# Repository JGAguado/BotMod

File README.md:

[![GitHub Release][releases-shield]][releases]
[![License][license-shield]](LICENSE)

[![Project Maintenance][maintenance-shield]][maintenance]
[![BuyMeCoffee][buymecoffee-shield]][buymecoffee]

# BotMod
Mod for ArduLab, directly plugable via the Mod Interface. The BotMod is designed to enhance the ArduLab functions for autonomous vehicles and printed-bots.

## Project tree

<li><a href="./Design/">Design</a></li>
<li><a href="./Documentation/">Documentation</a></li>

<li><a href="./README.md">README.md</a></li>

[releases-shield]: https://img.shields.io/github/release/JGAguado/BotMod.svg?style=for-the-badge
[releases]: https://github.com/JGAguado/BotMod/releases

[license-shield]: https://img.shields.io/badge/License-CC%20BY--NC--SA%204.0-lightgrey.svg?style=for-the-badge

[maintenance-shield]: https://img.shields.io/badge/maintainer-J.%20G.%20Aguado-blue.svg?style=for-the-badge
[maintenance]: https://github.com/JGAguado

[buymecoffee-shield]: https://img.shields.io/badge/buy%20me%20a%20coffee-support-yellow.svg?style=for-the-badge
[buymecoffee]: https://www.buymeacoffee.com/J.G.Aguado

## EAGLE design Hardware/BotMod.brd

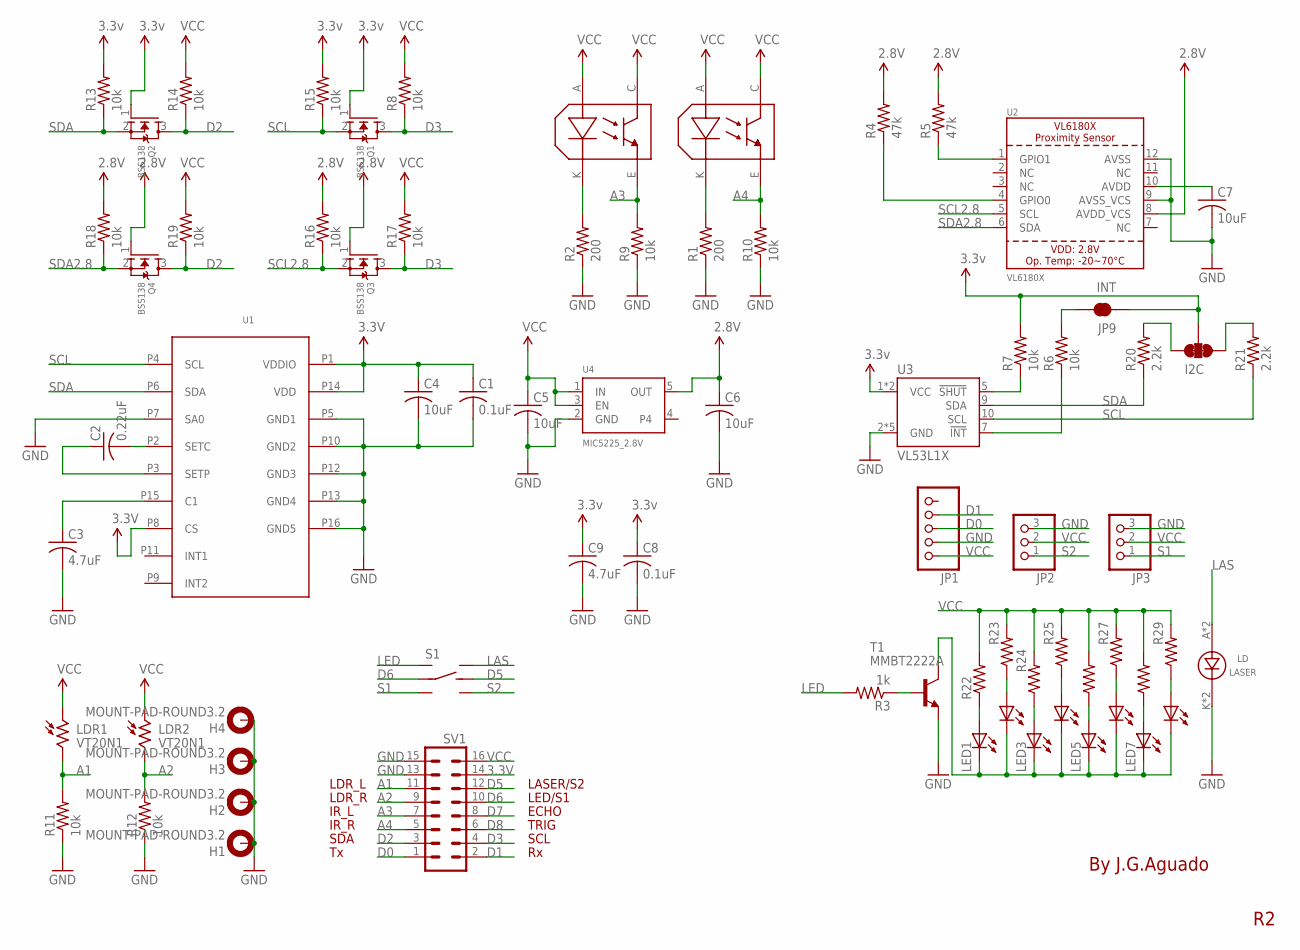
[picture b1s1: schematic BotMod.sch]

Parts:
C1, C8: 0.1uF; 0402
C2: 0.22uF; 0402
C3, C9: 4.7uF; 0402
C4, C5, C6, C7: 10uF; 0402
H1, H2, H3, H4: MOUNT-PAD-ROUND3.2; 3,2-PAD
I2C: JUMPER-SMT_3_2-NC_TRACE_SILK; SMT-JUMPER_3_2-NC_TRACE_SILK
IR1, IR2: IR_TCRT5000
JP1: PINHEAD_5_FEMALE
JP2, JP3: PINHD-1X3; 1X03
JP9: INT; PAD-JUMPER-2-NC_BY_TRACE_YES_SILK
LD: LASER; KEYES_LASER
LDR1, LDR2: VT20N1; TO46-VT200
LED1, LED2, LED3, LED4, LED5, LED6, LED7, LED8: LED5730
Q1, Q2, Q3, Q4: BSS138; SOT23
R1, R2: 200; 0402
R3: 1k; 0402
R4, R5: 47k; 0402
R6, R7, R8, R9, R10, R11, R12, R13, R14, R15, R16, R17, R18, R19: 10k; 0402
R20, R21: 2.2k; 0402
R22, R23, R24, R25, R26, R27, R28, R29: R1206; 1206
S1: DPDT_JS202011CQN
SV1: MA08-2
T1: MMBT2222A; SOT23-BEC
U1: LSM303D; LGA3X3_16L
U2: VL6180X; VL6180
U3: VL53L1X
U4: MIC5225_2.8V; SOT23-5

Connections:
2.8V: C6.1, Q3.1 (G), Q4.1 (G), R4.2, R5.2, R16.2, R18.2, U2.8 (AVDD_VCS), U4.5 (OUT)
3.3V: C1.1, C4.1, C8.1, C9.1, I2C.2, JP9.1, Q1.1 (G), Q2.1 (G), R7.2, R13.2, R15.2, SV1.14, U1.P1 (VDDIO), U1.P8 (CS), U1.P14 (VDD), U3.1 (VCC), U3.11 (VCC)
A1: LDR1.2, R11.2, SV1.11
A2: LDR2.2, R12.2, SV1.9
A3: IR1.E, R9.2, SV1.7
A4: IR2.E, R10.2, SV1.5
D0: JP1.P$3 (3), SV1.1
D1: JP1.P$4 (4), SV1.2
D2: Q2.3 (D), Q4.3 (D), R14.1, R19.1, SV1.3
D3: Q1.3 (D), Q3.3 (D), R8.1, R17.1, SV1.4
D5: S1.5 (RC), SV1.12
D6: S1.2 (LC), SV1.10
D7: SV1.8
D8: SV1.6
GND: C1.2, C3.2, C4.2, C5.2, C6.2, C7.2, C8.2, C9.2, H1.B3,2, H2.B3,2, H3.B3,2, H4.B3,2, JP1.P$2 (2), JP2.3, JP3.3, LD.K, LD.K1 (K), R1.1, R2.1, R9.1, R10.1, R11.1, R12.1, SV1.13, SV1.15, T1.E, U1.P5 (GND1), U1.P7 (SA0), U1.P10 (GND2), U1.P12 (GND3), U1.P13 (GND4), U1.P16 (GND5), U2.9 (AVSS_VCS), U2.12 (AVSS), U3.2 (GND), U3.3 (GND), U3.4 (GND), U3.6 (GND), U3.12 (GND), U4.2 (GND)
L1: LED1.P$1 (A), R22.1
L2: LED2.P$1 (A), R23.1
L3: LED3.P$1 (A), R24.1
L4: LED4.P$1 (A), R25.1
L5: LED5.P$1 (A), R26.1
L6: LED8.P$1 (A), R29.1
L7: LED7.P$1 (A), R28.1
L8: LED6.P$1 (A), R27.1
LAS: LD.A, LD.A1 (A), S1.4 (R1)
LED: R3.2, S1.1 (L1)
unnamed: LED1.P$2 (C), LED2.P$2 (C), LED3.P$2 (C), LED4.P$2 (C), LED5.P$2 (C), LED6.P$2 (C), LED7.P$2 (C), LED8.P$2 (C), T1.C
unnamed: R3.1, T1.B
unnamed: IR1.K, R2.2
unnamed: IR2.K, R1.2
unnamed: R5.1, U2.1 (GPIO1)
unnamed: R4.1, U2.4 (GPIO0)
unnamed: I2C.3, R20.2
unnamed: C7.1, U2.10 (AVDD)
unnamed: I2C.1, R21.2
unnamed: C3.1, U1.P15 (C1)
unnamed: C2.2, U1.P2 (SETC)
unnamed: C2.1, U1.P3 (SETP)
unnamed: JP9.2, R6.2
unnamed: R7.1, U3.5 (!SHUT)
unnamed: R6.1, U3.7 (!INT)
S1: JP3.1, S1.3 (L2)
S2: JP2.1, S1.6 (R2)
SCL: Q1.2 (S), R15.1, R21.1, U1.P4 (SCL), U3.10 (SCL)
SCL2.8: Q3.2 (S), R16.1, U2.5 (SCL)
SDA: Q2.2 (S), R13.1, R20.1, U1.P6 (SDA), U3.9 (SDA)
SDA2.8: Q4.2 (S), R18.1, U2.6 (SDA)
VCC: C5.1, IR1.A, IR1.C, IR2.A, IR2.C, JP1.P$1 (1), JP2.2, JP3.2, LDR1.1, LDR2.1, R8.2, R14.2, R17.2, R19.2, R22.2, R23.2, R24.2, R25.2, R26.2, R27.2, R28.2, R29.2, SV1.16, U4.1 (IN), U4.3 (EN)

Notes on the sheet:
SCL
By J.G.Aguado
SDA
LDR_L
LDR_R
IR_R
IR_L
TRIG
ECHO
LED/S1
LASER/S2

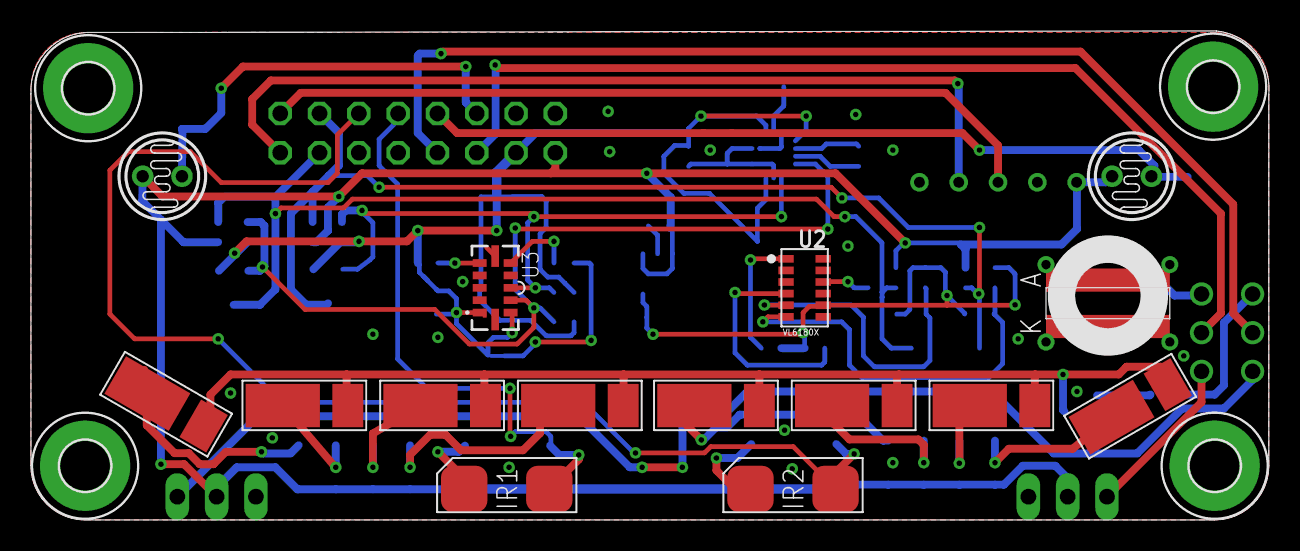
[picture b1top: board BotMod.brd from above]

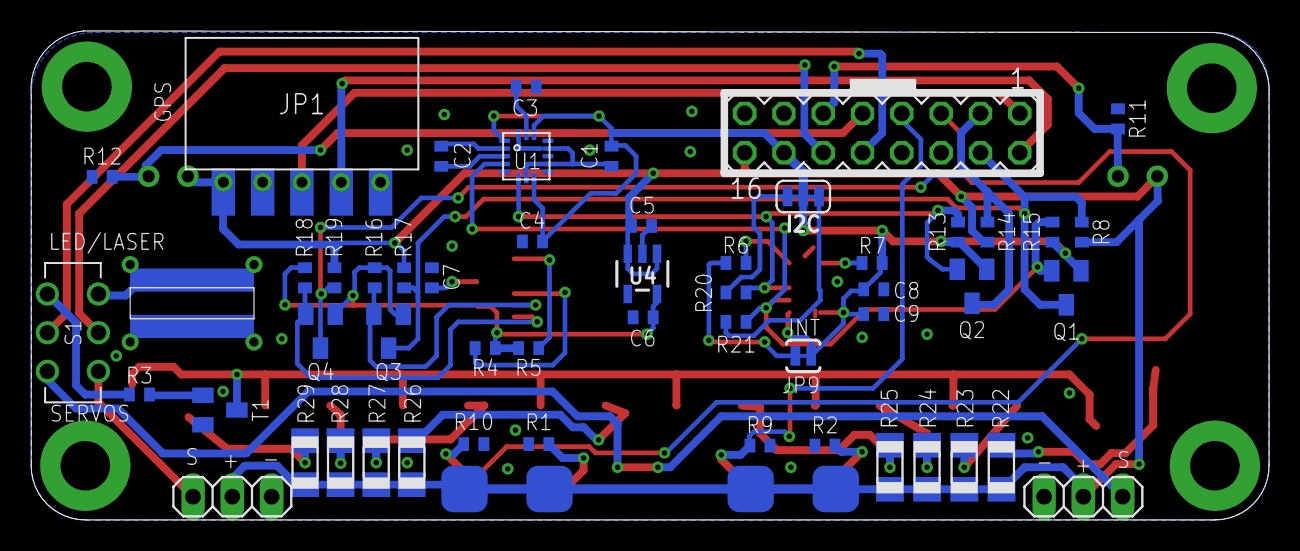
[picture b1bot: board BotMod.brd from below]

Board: 2 copper layers, 80.0 x 31.6 mm, 71 parts (52 on the bottom side), 45 nets.

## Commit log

2018-01-10 Laser resistor removed
2018-01-12 Mod connector updated to 16 pin
2018-01-14 SCH and BRD updated Production Files (GERBER, BOM and Centroid)
2018-01-17 Update gerber for production
2018-02-03 Added Schematic.pdf
2018-02-09 Updated centroid file
2018-04-29 Updated design files: - Added support for GPS through Serial port - Silkscreen layouts improved
2018-04-29 Production files updated
2018-05-02 Centroid file updated
2018-05-02 Updated documentation
2020-01-24 Redesigned BotMod (R2) with support for: - ToF distance sensors VL6180X (5-100mm) and VL53L1X (40-4000mm) - SMD High Intensity Led
2020-02-07 Updated LED Resistors
2020-02-28 Replaced LED lights with 7310 package
2020-02-28 Silkscreen files added
2020-02-28 Updated Production files
2020-05-10 Updated Design Files
2020-05-10 Removed Production zip
2022-04-15 Updated structure

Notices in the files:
parts and their libraries:
microbuilder: This work is placed in the public domain, and may be freely used for commercial and non-commercial work with the following conditions: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
SparkFun-Sensors: Licensing: Creative Commons ShareAlike 4.0 International - https://creativecommons.org/licenses/by-sa/4.0
